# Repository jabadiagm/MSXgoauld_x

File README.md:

# MSXgoauld_x
MSX Goa'uld board with Xilinx XC7A35T

MSX2+ engine in Z80 socket. It turns one MSX into an MSX2+ by replacing Z80 processor. FPGA in board contains: 
* Z80
* V9958 with hdmi output
* MSX2+ BIOS
* 4MB mapper
* RTC
* PSG through hdmi
* SCC (audio only) through hdmi
* OPLL through hdmi
* SD card interface with Nextor

## How it works:
Logic acts on bus control signals so that internal devices inside fpga take priority over external devices. 

## Slot map

Place SCC cartridges in slot 1 to get SCC sound through HDMI

## Revision 1 Board
PCB version 1 uses through hole components for ease of assembly

## Revision 2 Board

Revision 2 uses SOIC-20, TSSOP-20 for 74LS245 and 74LVC245 ICs, which are smaller:

## Bill of materials
Main elements:
* [QMTECH Xilinx FPGA Artix7 Artix-7 XC7A35T SDRAM Core Board](https://a.aliexpress.com/_EIR63QR)
* [(PCB V1) SD SPI or SDIO Card Breakout Board - 3V](https://a.aliexpress.com/_EJ8GIw7)
* [(PCB V1) HDMI female socket/plug 19P female mount 3-row pins](https://a.aliexpress.com/_Eub6hh9)
* [40Pin Connector Header Round Needle Gold Plated 1x40 Golden Pin Single Row Male 2.54mm Breakable Pin Connector Strip](https://a.aliexpress.com/_ExPDv4F)
* [dip 2*40/ PIN double row PIN HEADER 2.54MM PITCH MALE Strip Connector 2X](https://a.aliexpress.com/_EJbEXl9)
* [2.54mm Double Row Straight Female Pin Header Socket Connector 2x25Pin](https://a.aliexpress.com/_EvLvXL1)
* 2xSN74LVC245AN
* 3x74LS245
* Platform Cable USB II / DLC10 (programmer)

## Tips/Warnings
* HDMI circuitry is unprotected in V1 board, use at your own risk
* Turn on monitor after turning on MSX, otherwise fpga may not start
* When possible, use a linear power supply to keep electrical noises low
* Get integrated circuits from trusted sources
* Use turned pins in header to avoid damages in Z80 socket
* Board is sensitive to dirty electrical contacts, way more than Z80. Keep cartridge & Z80 socket contacts clean

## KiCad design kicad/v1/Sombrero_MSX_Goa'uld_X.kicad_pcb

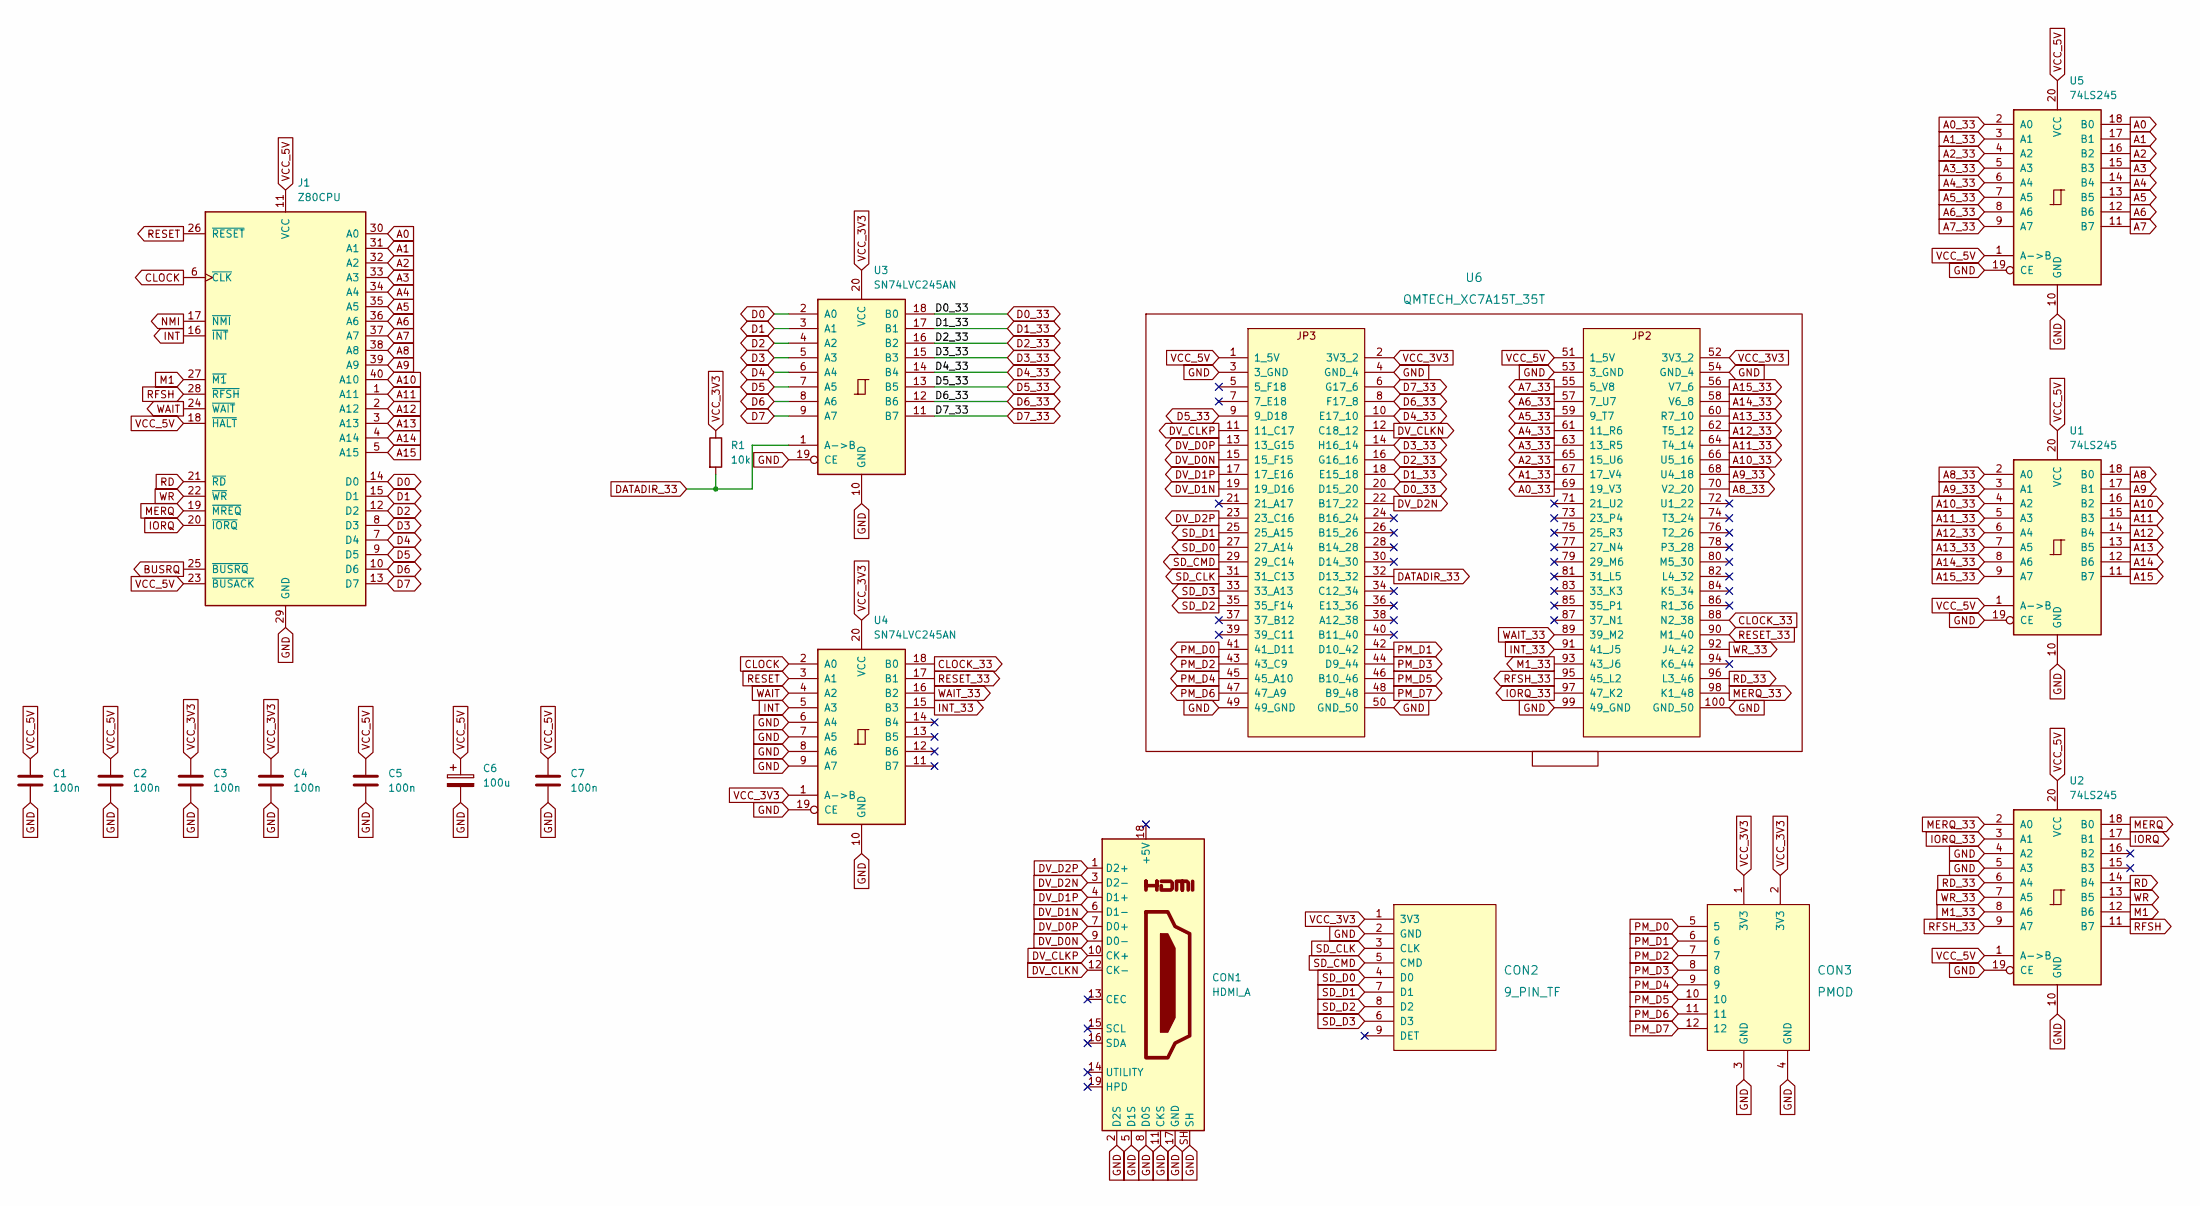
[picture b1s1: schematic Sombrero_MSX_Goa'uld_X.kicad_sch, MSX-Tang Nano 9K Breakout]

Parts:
C1, C2, C3, C4, C5, C7: 100n; C_Disc_D4.3mm_W1.9mm_P5.00mm
C6: 100u; CP_Radial_D5.0mm_P2.50mm
CON1: HDMI_A
CON2: 9_PIN_TF; 9_pin_tf
CON3: PMOD; PinHeader_2x06_P2.54mm_Vertical
J1: Z80CPU; DIP-40_W15.24mm_Socket
R1: 10k; R_Axial_DIN0207_L6.3mm_D2.5mm_P7.62mm_Horizontal
U1, U2, U5: 74LS245; DIP-20_W7.62mm_LongPads
U3, U4: SN74LVC245AN; DIP-20_W7.62mm_LongPads
U6: QMTECH_XC7A15T_35T

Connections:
A0: J1.30 (A0), U5.18 (B0)
A0_33: U5.2 (A0), U6.69 (19_V3)
A1: J1.31 (A1), U5.17 (B1)
A1_33: U5.3 (A1), U6.67 (17_V4)
A2: J1.32 (A2), U5.16 (B2)
A2_33: U5.4 (A2), U6.65 (15_U6)
A3: J1.33 (A3), U5.15 (B3)
A3_33: U5.5 (A3), U6.63 (13_R5)
A4: J1.34 (A4), U5.14 (B4)
A4_33: U5.6 (A4), U6.61 (11_R6)
A5: J1.35 (A5), U5.13 (B5)
A5_33: U5.7 (A5), U6.59 (9_T7)
A6: J1.36 (A6), U5.12 (B6)
A6_33: U5.8 (A6), U6.57 (7_U7)
A7: J1.37 (A7), U5.11 (B7)
A7_33: U5.9 (A7), U6.55 (5_V8)
A8: J1.38 (A8), U1.18 (B0)
A8_33: U1.2 (A0), U6.70 (V2_20)
A9: J1.39 (A9), U1.17 (B1)
A9_33: U1.3 (A1), U6.68 (U4_18)
A10: J1.40 (A10), U1.16 (B2)
A10_33: U1.4 (A2), U6.66 (U5_16)
A11: J1.1 (A11), U1.15 (B3)
A11_33: U1.5 (A3), U6.64 (T4_14)
A12: J1.2 (A12), U1.14 (B4)
A12_33: U1.6 (A4), U6.62 (T5_12)
A13: J1.3 (A13), U1.13 (B5)
A13_33: U1.7 (A5), U6.60 (R7_10)
A14: J1.4 (A14), U1.12 (B6)
A14_33: U1.8 (A6), U6.58 (V6_8)
A15: J1.5 (A15), U1.11 (B7)
A15_33: U1.9 (A7), U6.56 (V7_6)
BUSRQ: J1.25 (~BUSRQ)
CLOCK: J1.6 (~CLK), U4.2 (A0)
CLOCK_33: U4.18 (B0), U6.88 (N2_38)
D0: J1.14 (D0), U3.2 (A0)
D0_33: U3.18 (B0), U6.20 (D15_20)
D1: J1.15 (D1), U3.3 (A1)
D1_33: U3.17 (B1), U6.18 (E15_18)
D2: J1.12 (D2), U3.4 (A2)
D2_33: U3.16 (B2), U6.16 (G16_16)
D3: J1.8 (D3), U3.5 (A3)
D3_33: U3.15 (B3), U6.14 (H16_14)
D4: J1.7 (D4), U3.6 (A4)
D4_33: U3.14 (B4), U6.10 (E17_10)
D5: J1.9 (D5), U3.7 (A5)
D5_33: U3.13 (B5), U6.9 (9_D18)
D6: J1.10 (D6), U3.8 (A6)
D6_33: U3.12 (B6), U6.8 (F17_8)
D7: J1.13 (D7), U3.9 (A7)
D7_33: U3.11 (B7), U6.6 (G17_6)
DATADIR_33: R1.2, U3.1 (A->B), U6.32 (D13_32)
DV_CLKN: CON1.12 (CK-), U6.12 (C18_12)
DV_CLKP: CON1.10 (CK+), U6.11 (11_C17)
DV_D0N: CON1.9 (D0-), U6.15 (15_F15)
DV_D0P: CON1.7 (D0+), U6.13 (13_G15)
DV_D1N: CON1.6 (D1-), U6.19 (19_D16)
DV_D1P: CON1.4 (D1+), U6.17 (17_E16)
DV_D2N: CON1.3 (D2-), U6.22 (B17_22)
DV_D2P: CON1.1 (D2+), U6.23 (23_C16)
GND: C1.2, C2.2, C3.2, C4.2, C5.2, C6.2, C7.2, CON1.2 (D2S), CON1.5 (D1S), CON1.8 (D0S), CON1.11 (CKS), CON1.17 (GND), CON1.SH, CON2.2 (GND), CON3.3 (GND), CON3.4 (GND), J1.29 (GND), U1.10 (GND), U1.19 (CE), U2.4 (A2), U2.5 (A3), U2.10 (GND), U2.19 (CE), U3.10 (GND), U3.19 (CE), U4.6 (A4), U4.7 (A5), U4.8 (A6), U4.9 (A7), U4.10 (GND), U4.19 (CE), U5.10 (GND), U5.19 (CE), U6.3 (3_GND), U6.4 (GND_4), U6.49 (49_GND), U6.50 (GND_50), U6.53 (3_GND), U6.54 (GND_4), U6.99 (49_GND), U6.100 (GND_50)
INT: J1.16 (~INT), U4.5 (A3)
INT_33: U4.15 (B3), U6.91 (41_J5)
IORQ: J1.20 (~IORQ), U2.17 (B1)
IORQ_33: U2.3 (A1), U6.97 (47_K2)
M1: J1.27 (~M1), U2.12 (B6)
M1_33: U2.8 (A6), U6.93 (43_J6)
MERQ: J1.19 (~MREQ), U2.18 (B0)
MERQ_33: U2.2 (A0), U6.98 (K1_48)
NMI: J1.17 (~NMI)
PM_D0: CON3.5, U6.41 (41_D11)
PM_D1: CON3.6, U6.42 (D10_42)
PM_D2: CON3.7, U6.43 (43_C9)
PM_D3: CON3.8, U6.44 (D9_44)
PM_D4: CON3.9, U6.45 (45_A10)
PM_D5: CON3.10, U6.46 (B10_46)
PM_D6: CON3.11, U6.47 (47_A9)
PM_D7: CON3.12, U6.48 (B9_48)
RD: J1.21 (~RD), U2.14 (B4)
RD_33: U2.6 (A4), U6.96 (L3_46)
RESET: J1.26 (~RESET), U4.3 (A1)
RESET_33: U4.17 (B1), U6.90 (M1_40)
RFSH: J1.28 (~RFSH), U2.11 (B7)
RFSH_33: U2.9 (A7), U6.95 (45_L2)
SD_CLK: CON2.3 (CLK), U6.31 (31_C13)
SD_CMD: CON2.5 (CMD), U6.29 (29_C14)
SD_D0: CON2.4 (D0), U6.27 (27_A14)
SD_D1: CON2.7 (D1), U6.25 (25_A15)
SD_D2: CON2.8 (D2), U6.35 (35_F14)
SD_D3: CON2.6 (D3), U6.33 (33_A13)
VCC_3V3: C3.1, C4.1, CON2.1 (3V3), CON3.1 (3V3), CON3.2 (3V3), R1.1, U3.20 (VCC), U4.1 (A->B), U4.20 (VCC), U6.2 (3V3_2), U6.52 (3V3_2)
VCC_5V: C1.1, C2.1, C5.1, C6.1, C7.1, J1.11 (VCC), J1.18 (~HALT), J1.23 (~BUSACK), U1.1 (A->B), U1.20 (VCC), U2.1 (A->B), U2.20 (VCC), U5.1 (A->B), U5.20 (VCC), U6.1 (1_5V), U6.51 (1_5V)
WAIT: J1.24 (~WAIT), U4.4 (A2)
WAIT_33: U4.16 (B2), U6.89 (39_M2)
WR: J1.22 (~WR), U2.13 (B5)
WR_33: U2.7 (A5), U6.92 (J4_42)

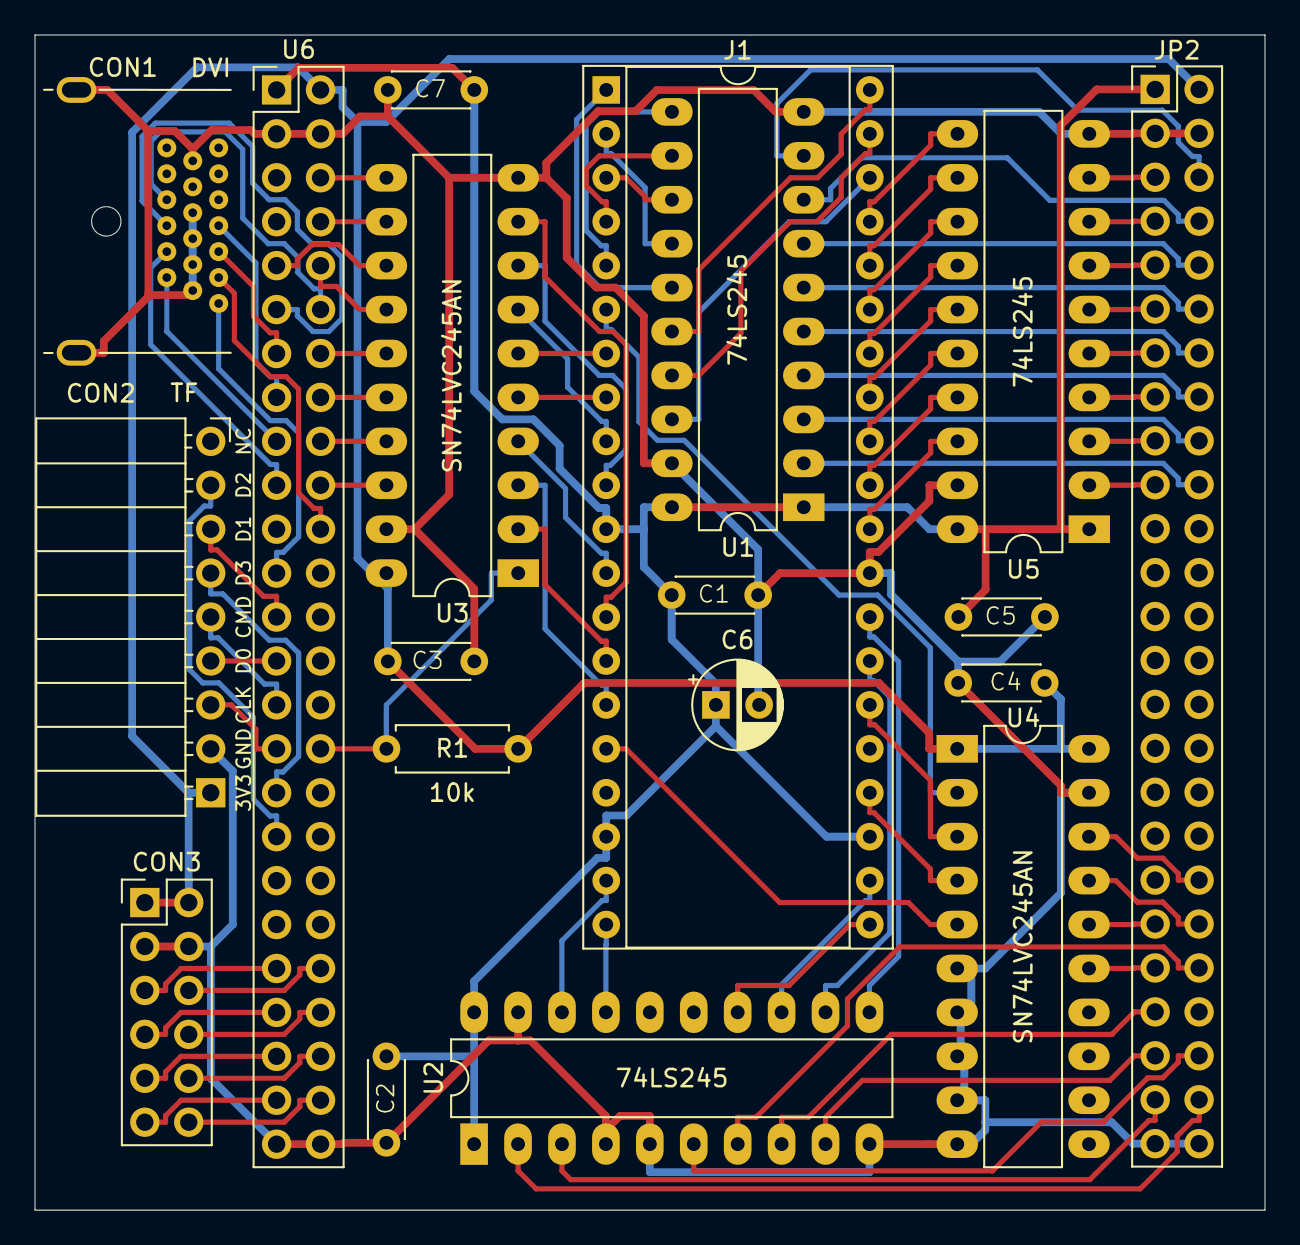
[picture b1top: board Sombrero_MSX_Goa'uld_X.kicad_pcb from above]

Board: 2 copper layers, 71.1 x 67.9 mm, 18 parts (0 on the bottom side), 94 nets.

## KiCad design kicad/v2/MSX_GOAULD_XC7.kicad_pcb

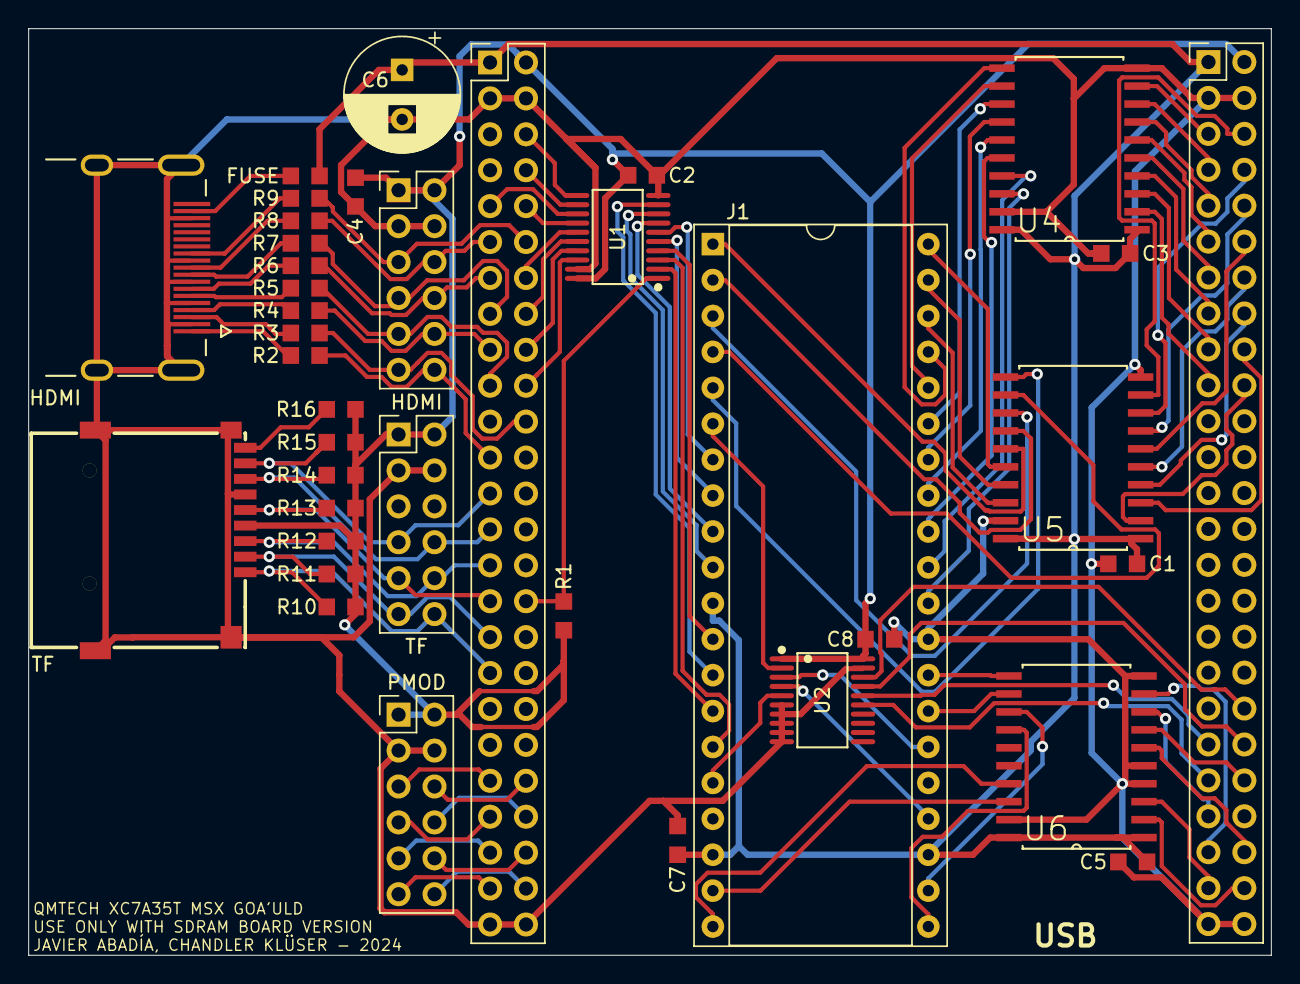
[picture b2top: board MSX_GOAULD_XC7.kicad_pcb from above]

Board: 2 copper layers, 87.9 x 65.5 mm, 37 parts (0 on the bottom side), 104 nets.

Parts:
C1, C2, C3, C4, C5, C7: 100n; SMD_RES_1
C6: 100u; CP_Radial_D8.0mm_P3.50mm
C8: 0.1uF; SMD_RES_1
FUSE: FUSE; SMD_RES_1
HDMI: 2086581051; HDMI
HDMI#2: PMOD_DVI; PMOD
J1: Z80CPU; DIP-40_W15.24mm_Socket
PMOD: PMOD
R1: 10k; SMD_RES_1
R2, R3, R4, R5, R6, R7, R8, R9: 270R; SMD_RES_1
R10, R11, R12, R13, R14, R15, R16: 4.7k; SMD_RES_1
TF: TF-CARD H1.8 SY; TF-SMD_TF-012
TF#2: PMOD_TF; PMOD
U1, U2: SN74LVC245AN; TSSOP-20
U3: QMTECH_XC7A15T_35T
U4, U5, U6: 74LS245; SOIC127P1032X265-20N

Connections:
A0: J1.30 (A0), U4.18 (B0)
A0_33: U3.69 (19_V3), U4.2 (A0)
A1: J1.31 (A1), U4.17 (B1)
A1_33: U3.67 (17_V4), U4.3 (A1)
A2: J1.32 (A2), U4.16 (B2)
A2_33: U3.65 (15_U6), U4.4 (A2)
A3: J1.33 (A3), U4.15 (B3)
A3_33: U3.63 (13_R5), U4.5 (A3)
A4: J1.34 (A4), U4.14 (B4)
A4_33: U3.61 (11_R6), U4.6 (A4)
A5: J1.35 (A5), U4.13 (B5)
A5_33: U3.59 (9_T7), U4.7 (A5)
A6: J1.36 (A6), U4.12 (B6)
A6_33: U3.57 (7_U7), U4.8 (A6)
A7: J1.37 (A7), U4.11 (B7)
A7_33: U3.55 (5_V8), U4.9 (A7)
A8: J1.38 (A8), U5.18 (B0)
A8_33: U3.70 (V2_20), U5.2 (A0)
A9: J1.39 (A9), U5.17 (B1)
A9_33: U3.68 (U4_18), U5.3 (A1)
A10: J1.40 (A10), U5.16 (B2)
A10_33: U3.66 (U5_16), U5.4 (A2)
A11: J1.1 (A11), U5.15 (B3)
A11_33: U3.64 (T4_14), U5.5 (A3)
A12: J1.2 (A12), U5.14 (B4)
A12_33: U3.62 (T5_12), U5.6 (A4)
A13: J1.3 (A13), U5.13 (B5)
A13_33: U3.60 (R7_10), U5.7 (A5)
A14: J1.4 (A14), U5.12 (B6)
A14_33: U3.58 (V6_8), U5.8 (A6)
A15: J1.5 (A15), U5.11 (B7)
A15_33: U3.56 (V7_6), U5.9 (A7)
CLOCK: J1.6 (~CLK), U2.2 (A0)
CLOCK_33: U2.18 (B0), U3.88 (N2_38)
D0: J1.14 (D0), U1.2 (A0)
D0_33: U1.18 (B0), U3.20 (D15_20)
D1: J1.15 (D1), U1.3 (A1)
D1_33: U1.17 (B1), U3.18 (E15_18)
D2: J1.12 (D2), U1.4 (A2)
D2_33: U1.16 (B2), U3.16 (G16_16)
D3: J1.8 (D3), U1.5 (A3)
D3_33: U1.15 (B3), U3.14 (H16_14)
D4: J1.7 (D4), U1.6 (A4)
D4_33: U1.14 (B4), U3.10 (E17_10)
D5: J1.9 (D5), U1.7 (A5)
D5_33: U1.13 (B5), U3.9 (9_D18)
D6: J1.10 (D6), U1.8 (A6)
D6_33: U1.12 (B6), U3.8 (F17_8)
D7: J1.13 (D7), U1.9 (A7)
D7_33: U1.11 (B7), U3.6 (G17_6)
DATADIR_33: R1.2, U1.1 (A->B), U3.32 (D13_32)
DV_CLKN: HDMI#2.5 (CKN), R9.1, U3.12 (C18_12)
DV_CLKP: HDMI#2.6 (CKP), R8.1, U3.11 (11_C17)
DV_D0N: HDMI#2.7 (D0N), R7.1, U3.15 (15_F15)
DV_D0P: HDMI#2.8 (D0P), R6.1, U3.13 (13_G15)
DV_D1N: HDMI#2.9 (D1N), R5.1, U3.19 (19_D16)
DV_D1P: HDMI#2.10 (D1P), R4.1, U3.17 (17_E16)
DV_D2N: HDMI#2.11 (D2N), R3.1, U3.22 (B17_22)
DV_D2P: HDMI#2.12 (D2P), R2.1, U3.23 (23_C16)
GND: C1.2, C2.2, C3.2, C4.2, C5.2, C6.2, C7.2, C8.1, HDMI.2, HDMI.5, HDMI.8, HDMI.11, HDMI.17, HDMI.SH1 (SHIELD1), HDMI.SH2 (SHIELD2), HDMI.SH3 (SHIELD3), HDMI.SH4 (SHIELD4), HDMI#2.3 (GND), HDMI#2.4 (GND), J1.29 (GND), PMOD.3 (GND), PMOD.4 (GND), TF.6 (VSS), TF.10 (GND), TF.11 (GND), TF.12 (GND), TF.13 (GND), TF#2.3 (GND), TF#2.4 (GND), U1.10 (GND), U1.19 (CE), U2.6 (A4), U2.7 (A5), U2.8 (A6), U2.9 (A7), U2.10 (GND), U2.19 (CE), U3.3 (3_GND), U3.4 (GND_4), U3.49 (49_GND), U3.50 (GND_50), U3.53 (3_GND), U3.54 (GND_4), U3.99 (49_GND), U3.100 (GND_50), U4.10 (GND), U4.19 (CE), U5.10 (GND), U5.19 (CE), U6.4 (A2), U6.5 (A3), U6.10 (GND), U6.19 (CE)
INT: J1.16 (~INT), U2.5 (A3)
INT_33: U2.15 (B3), U3.91 (41_J5)
IORQ: J1.20 (~IORQ), U6.17 (B1)
IORQ_33: U3.97 (47_K2), U6.3 (A1)
M1: J1.27 (~M1), U6.12 (B6)
M1_33: U3.93 (43_J6), U6.8 (A6)
MERQ: J1.19 (~MREQ), U6.18 (B0)
MERQ_33: U3.98 (K1_48), U6.2 (A0)
unnamed: FUSE.2, HDMI.18
unnamed: HDMI.1, R2.2
unnamed: HDMI.3, R3.2
unnamed: HDMI.4, R4.2
unnamed: HDMI.6, R5.2
unnamed: HDMI.7, R6.2
unnamed: HDMI.9, R7.2
unnamed: HDMI.10, R8.2
unnamed: HDMI.12, R9.2
unnamed: R16.2, TF.9 (CD)
PM_D0: PMOD.5, U3.41 (41_D11)
PM_D1: PMOD.6, U3.42 (D10_42)
PM_D2: PMOD.7, U3.43 (43_C9)
PM_D3: PMOD.8, U3.44 (D9_44)
PM_D4: PMOD.9, U3.45 (45_A10)
PM_D5: PMOD.10, U3.46 (B10_46)
PM_D6: PMOD.11, U3.47 (47_A9)
PM_D7: PMOD.12, U3.48 (B9_48)
RD: J1.21 (~RD), U6.14 (B4)
RD_33: U3.96 (L3_46), U6.6 (A4)
RESET: J1.26 (~RESET), U2.3 (A1)
RESET_33: U2.17 (B1), U3.90 (M1_40)
RFSH: J1.28 (~RFSH), U6.11 (B7)
RFSH_33: U3.95 (45_L2), U6.9 (A7)
SD_CLK: R13.1, TF.5 (CLK), TF#2.9 (CLK), U3.31 (31_C13)
SD_CMD: R12.1, TF.3 (CMD), TF#2.10 (CMD), U3.29 (29_C14)
SD_D0: R14.1, TF.7 (DAT0), TF#2.8 (D0), U3.27 (27_A14)
SD_D1: R15.1, TF.8 (DAT1), TF#2.7 (D1), U3.25 (25_A15)
SD_D2: R10.1, TF.1 (DAT2), TF#2.12 (D2), U3.35 (35_F14)
SD_D3: R11.1, TF.2 (CD/DAT3), TF#2.11 (D3), U3.33 (33_A13)
VCC_3V3: C2.1, C4.1, C8.2, HDMI#2.1 (3V3), HDMI#2.2 (3V3), PMOD.1 (3V3), PMOD.2 (3V3), R1.1, R10.2, R11.2, R12.2, R13.2, R14.2, R15.2, R16.1, TF.4 (VDD), TF#2.1 (3V3), TF#2.2 (3V3), U1.20 (VCC), U2.1 (A->B), U2.20 (VCC), U3.2 (3V3_2), U3.52 (3V3_2)
VCC_5V: C1.1, C3.1, C5.1, C6.1, C7.1, FUSE.1, J1.11 (VCC), J1.18 (~HALT), J1.23 (~BUSACK), U3.1 (1_5V), U3.51 (1_5V), U4.1 (A->B), U4.20 (VCC), U5.1 (A->B), U5.20 (VCC), U6.1 (A->B), U6.20 (VCC)
WAIT: J1.24 (~WAIT), U2.4 (A2)
WAIT_33: U2.16 (B2), U3.89 (39_M2)
WR: J1.22 (~WR), U6.13 (B5)
WR_33: U3.92 (J4_42), U6.7 (A5)

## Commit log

2024-06-22 22/06/2024 Version 0.5 Initial
2024-07-15 Fixed wrong reference
